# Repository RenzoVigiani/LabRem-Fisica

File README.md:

# Laboratorios de Física básica
En este readme se detallan las partes mas importantes del proyecto de remotización del laboratorio de física básica, haciendo énfacis en el hardware.

## Protocolo para los laboratorios de "Física básica"
Para poder establecer una comunicación entre al api web, generada por el equipo de software del proyecto, y los dispositivos en el laboratorio establecemos un protocolo en común. 

El procedimiento de comunicación es el siguiente. Cada vez que se quiere modificar algun dato en el laboratorio. El Servidor debe enviar un:
```Ruby 
POST /HTTP/1.1 + <JSON a enviar>
```
#### Json a enviar (ejemplo)
```Ruby  
{ "Estado": [0,true,false],"Analogico": [1,125,542,2]}
```
Y para obtener avances de los datos o reporte de los datos debe enviar un:
```Ruby 
GET /HTTP/1.1
```
De esta forma el Arduino responde ante una petición.

#### Json a recibir (ejemplo)

```Ruby  
{ "Estado": [0,true,false],"Analogico": [1,125,542,2], "Error": "Mensaje de error"}
```

## Sintaxis

**Estado:** Es un array conformado por 3 elementos en el siguiente orden: [Laboratorio, SubLab, Inicio del experimento]

|Laboratorio  | Sub Laboratorio  | Inicio del experimento | Laboratorio Seleccionado | Estado del experimento|
|-|-----|-----|-----------------|--------|
|3|true |true |Lente Convergente|Inicia  |
|3|true |false|Lente Convergente|Finaliza|
|3|false|true |Lente Divergente |Inicia  |
|3|false|false|Lente Divergente |Finaliza|

**Elementos por Laboratorio**

***Convergente***

- Analogico: [Tipo_Diafragma,Distancia_FL,Distancia_LP]
    
    Distancia_FL: Corresponde a la distancia entre Foco y Lente.
    
    Distancia_LP: Corresponde a la distancia entre Lente y Pantalla.

- Tipo_Diafragma = Indica el tipo de diafragma
  - 0 : Sin diafragma
  - 1 : Central
  - 2 : Periferico
  - 3 : Filtro Rojo

***Divergente***

```Ruby 
Analogico:[Tipo_Diafragma, Distancia_FL1, Distancia_L2P, Distancia_L1L2]
```
- Distancia_FL1: Corresponde a la distancia entre Foco y Lente Divergente.
- Distancia_L2P: Corresponde a la distancia entre Lente convergente y Pantalla.
- Distancia_L1L2: Corresponde a la distancia entre Lente divergente y convergente.

## Valores permitidos

Los valores permitidos en las distancias son:

| Distancia          |Valor mín|Valor máx| Unidad |
| ------------------ |---------|---------|--------|
|FL: Foco Lente      |   120   |   970   |  [mm]  |
|LP: Lente Pantalla  |    70   |   970   |  [mm]  |
|FL1: Foco Lente1    |    50   |   920   |  [mm]  |
|L1L2: Lente1 Lente2 |    70   |   900   |  [mm]  |
|L2P: Lente2 Pantalla|    70   |   970   |  [mm]  |

Se puede observar en la imagen las distancias especificadas. Se consideran margenes entre los soportes por seguridad.

**Error:** Es una variable numerica que representa un mensaje de error. 

| Tipo de error                     |  Valor  |
|-----------------------------------|---------|
| Sin errores                       |    0    |
| Error de distancia                |    1    |
| Error de tipo de diafragma        |    2    |
| Error de laboratorio incorrecto   |    3    |

## Diagramas
Para poder conectar la api web con los actuadores utilizamos un Arduino Mega 2560 y una placa creada por el equipo de hardware. 

Esta placa incorpora todos los drivers e indicadores necesarios para el funcionamiento del laboratorio.

**Arduino Mega 2560: PinOut**

||**ESQUEMÁTICO**||
|-|-|-|
||||

||**PCB**||
|-|-|-|
||||
||||
||||
||||
||||

**Diagrama general**

**Diagrama Vista superior**

**Diagrama Vista frontal**

**Datasheets Actuadores**
- [Recopilación de Datasheets](https://renzovigiani.notion.site/adea4f735c994faaa2f919a7e5105e9d?v=83070c8c05d34c02905fc370e37b802a)
- [Servo Motor MG966R](https://github.com/RenzoVigiani/LabRem-Fisica/blob/main/datasheets/MG996R-Datasheet.pdf)
- [Motor Paso a paso](https://github.com/RenzoVigiani/LabRem-Fisica/blob/main/datasheets/MG996R-Datasheet.pdf)
- [Lampara Led](http://wayjun.com/Datasheet/Led/3W%20High%20Power%20LED.pdf)

**Soportes 3D**

 A continuación se pueden ver los elementos diseñados por el equipo de hardware y luego creados a partir de una impresora 3D. Esto permitió generar soportes y gabinetes de acuerdo a los requerimientos y logrando mayor flexibilidad.

Se pueden ver los soportes creados para el sistema de movimiento de todo el ensayo. Se muestran:
- 4 bases para las lentes y el movimiento sobre los rieles.
- 3 soportes para motores paso a paso.
- 1 gabinete para soporte de foco o fuente de luz.
- 1 soporte para la pantalla.

|            |   |
|-------------------------|---------|
|   |    |
| ||
|   |   |
|  |  |
|  |  |
|  |  |

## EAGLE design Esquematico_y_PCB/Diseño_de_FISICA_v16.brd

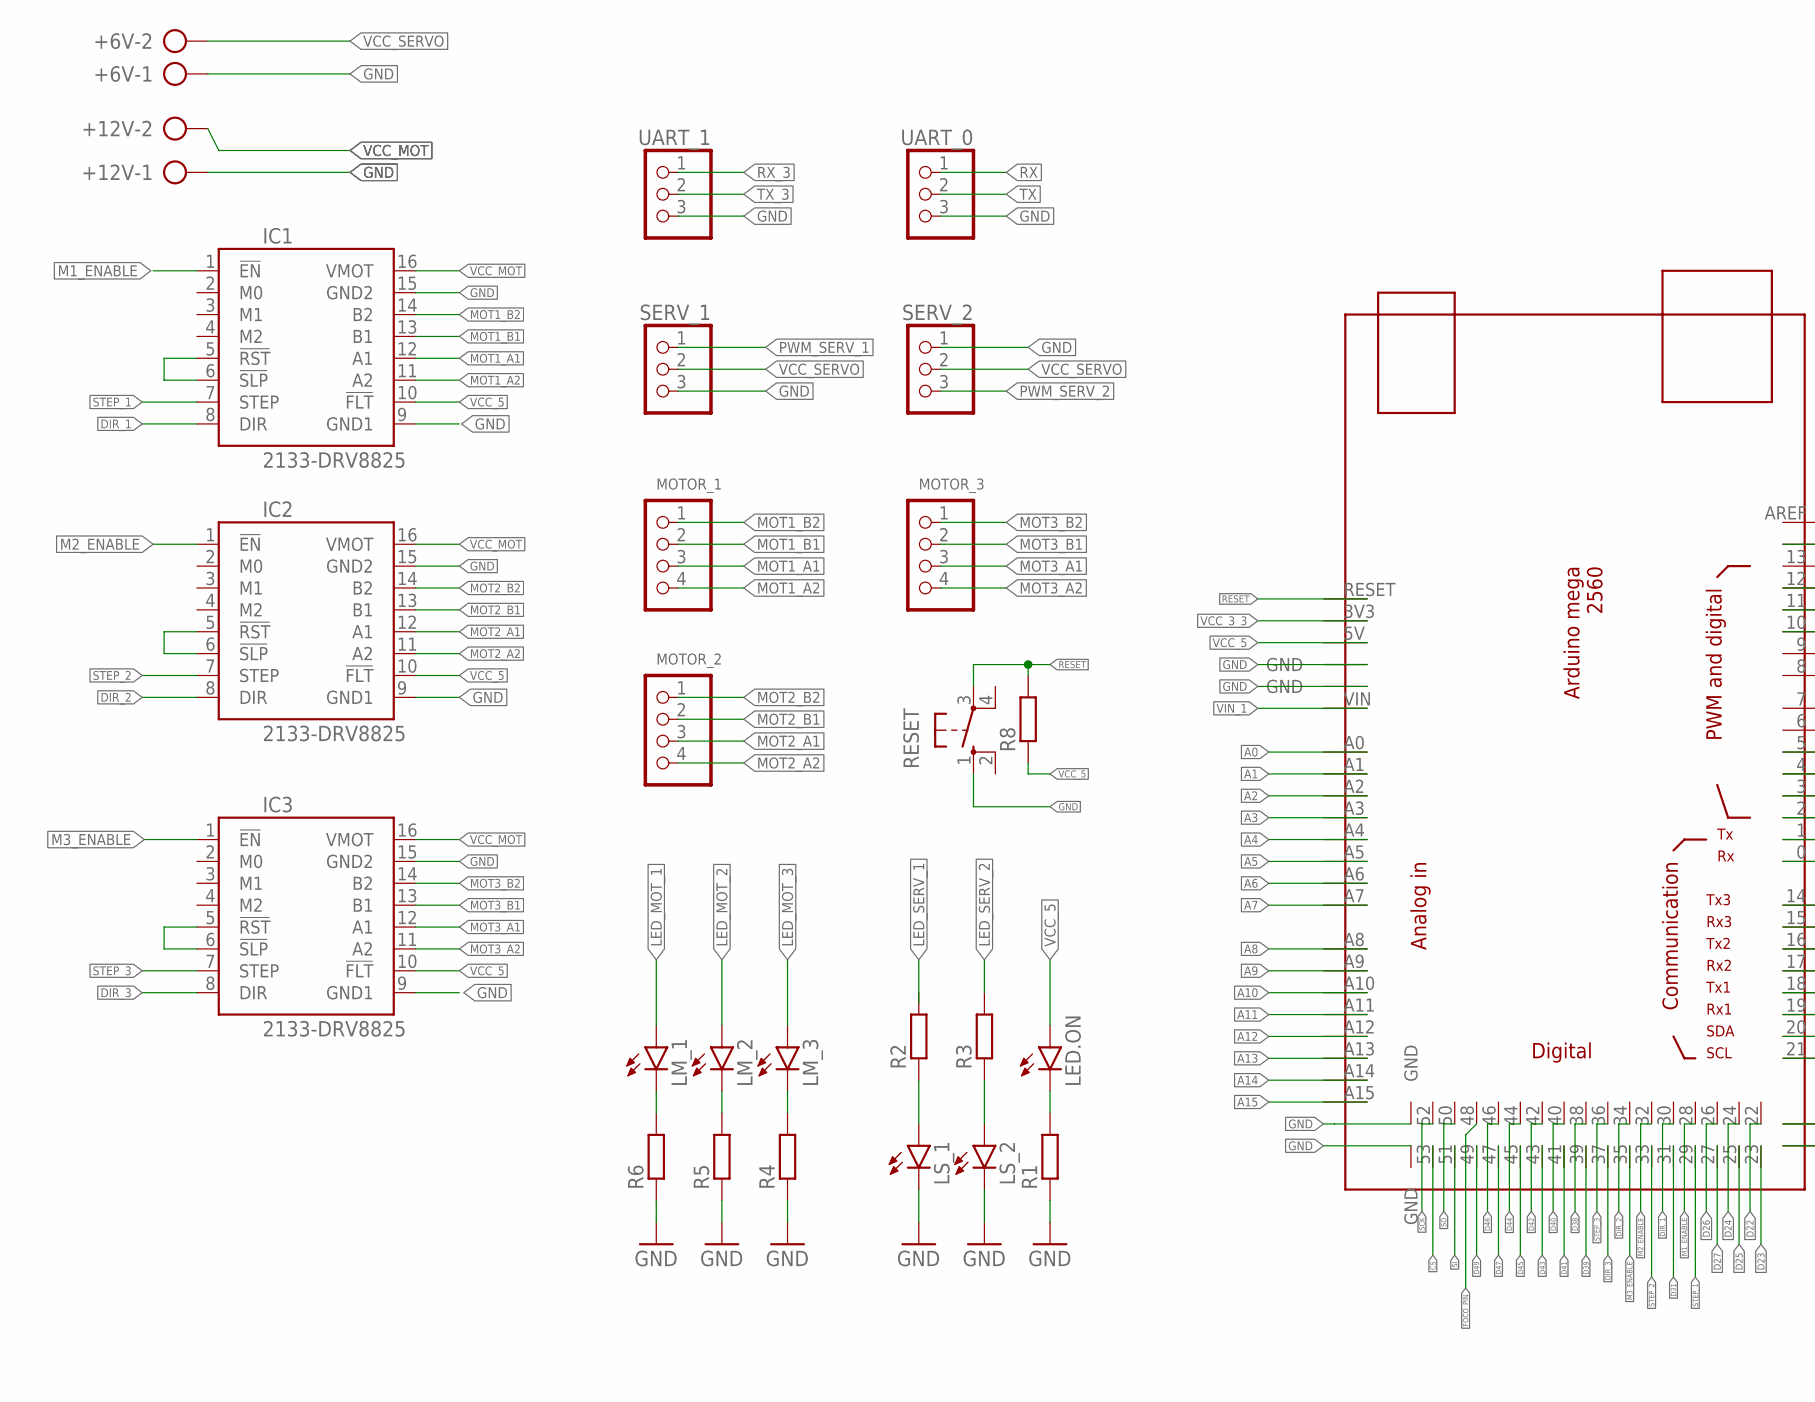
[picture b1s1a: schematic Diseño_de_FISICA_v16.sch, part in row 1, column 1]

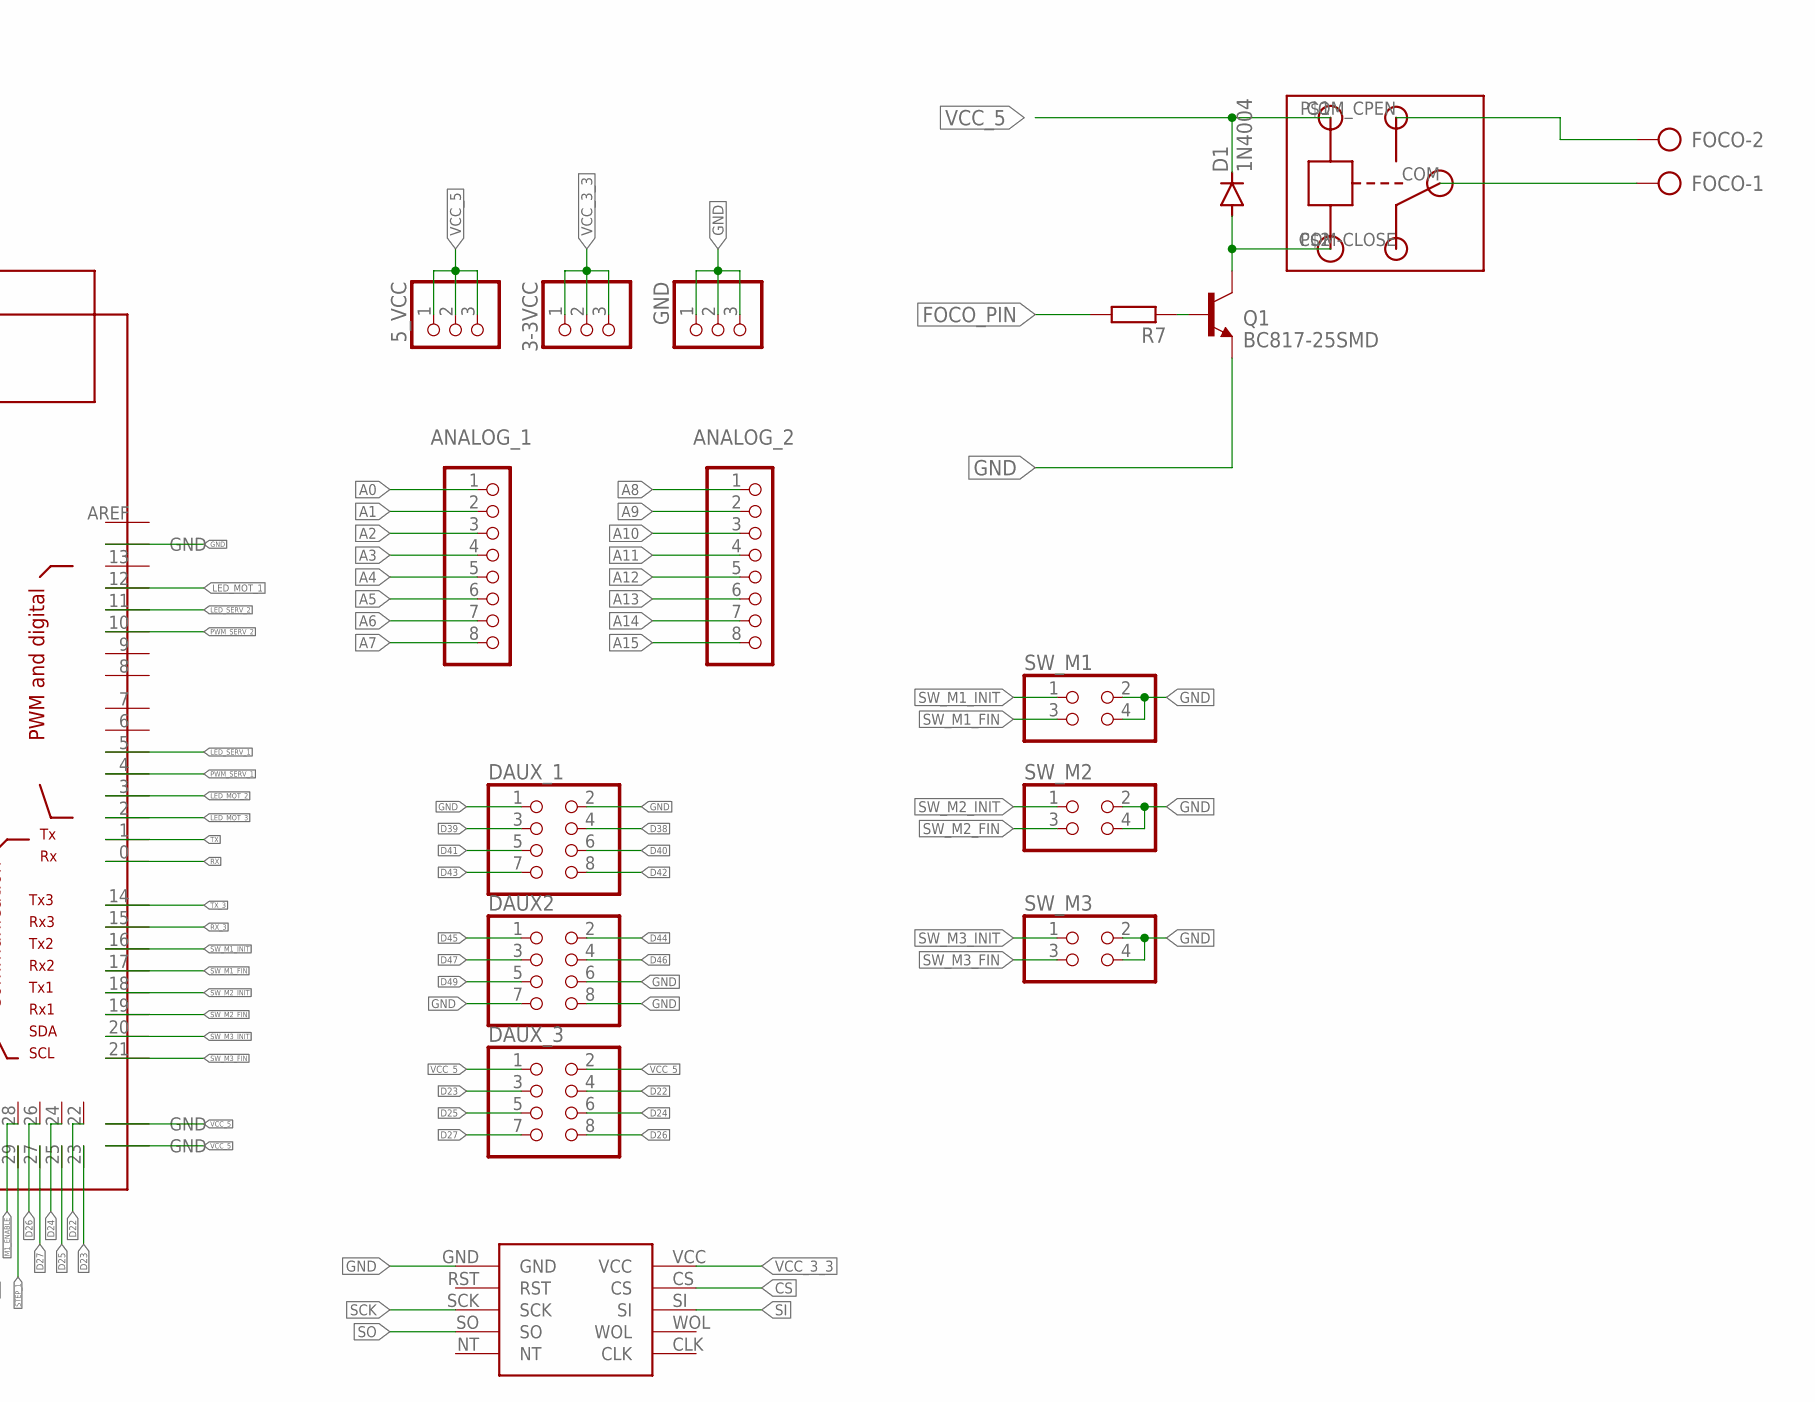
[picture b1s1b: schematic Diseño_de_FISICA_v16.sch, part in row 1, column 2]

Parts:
3-3VCC, 5_VCC: PINHD-1X3; 1X03
+6V, +12V: AK300/2
ANALOG_1, ANALOG_2: PINHD-1X8; 1X08
ARDUINOMEGA2560: MEGA_DEVICE; MEGAOUTLINE
D1: 1N4004; DO41-10
DAUX2: PINHD-2X4; 2X04
DAUX_1, DAUX_3: PINHD-2X4; 2X04
FOCO: AK300/2
GND: PINHD-1X3; 1X03
IC1, IC2, IC3: 2133-DRV8825; DRV8825
LED.ON: LED3MM
LM_1, LM_2, LM_3: LED3MM
LS_1, LS_2: LED3MM
MODULO_ETHERNET: ENC28J60
MOTOR_1, MOTOR_2, MOTOR_3: PINHD-1X4; 1X04
Q1: BC817-25SMD; SOT23-BEC
R1, R2, R3, R4, R5, R6, R7, R8: R_CHIP-0805(2012-METRIC); RESC2012X65
RESET: 10-XX; B3F-10XX
SERV_1, SERV_2: PINHD-1X3; 1X03
SW_M1, SW_M2, SW_M3: PINHD-2X2; 2X02
U$1: RELAY
UART_0, UART_1: PINHD-1X3; 1X03

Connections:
A0: ANALOG_1.1, ARDUINOMEGA2560.A0
A1: ANALOG_1.2, ARDUINOMEGA2560.A1
A2: ANALOG_1.3, ARDUINOMEGA2560.A2
A3: ANALOG_1.4, ARDUINOMEGA2560.A3
A4: ANALOG_1.5, ARDUINOMEGA2560.A4
A5: ANALOG_1.6, ARDUINOMEGA2560.A5
A6: ANALOG_1.7, ARDUINOMEGA2560.A6
A7: ANALOG_1.8, ARDUINOMEGA2560.A7
A8: ANALOG_2.1, ARDUINOMEGA2560.A8
A9: ANALOG_2.2, ARDUINOMEGA2560.A9
A10: ANALOG_2.3, ARDUINOMEGA2560.A10
A11: ANALOG_2.4, ARDUINOMEGA2560.A11
A12: ANALOG_2.5, ARDUINOMEGA2560.A12
A13: ANALOG_2.6, ARDUINOMEGA2560.A13
A14: ANALOG_2.7, ARDUINOMEGA2560.A14
A15: ANALOG_2.8, ARDUINOMEGA2560.A15
CS: ARDUINOMEGA2560.53, MODULO_ETHERNET.CS
D22: ARDUINOMEGA2560.22, DAUX_3.4
D23: ARDUINOMEGA2560.23, DAUX_3.3
D24: ARDUINOMEGA2560.24, DAUX_3.6
D25: ARDUINOMEGA2560.25, DAUX_3.5
D26: ARDUINOMEGA2560.26, DAUX_3.8
D27: ARDUINOMEGA2560.27, DAUX_3.7
D31: ARDUINOMEGA2560.31
D38: ARDUINOMEGA2560.38, DAUX_1.4
D39: ARDUINOMEGA2560.39, DAUX_1.3
D40: ARDUINOMEGA2560.40, DAUX_1.6
D41: ARDUINOMEGA2560.41, DAUX_1.5
D42: ARDUINOMEGA2560.42, DAUX_1.8
D43: ARDUINOMEGA2560.43, DAUX_1.7
D44: ARDUINOMEGA2560.44, DAUX2.2
D45: ARDUINOMEGA2560.45, DAUX2.1
D46: ARDUINOMEGA2560.46, DAUX2.4
D47: ARDUINOMEGA2560.47, DAUX2.3
D49: ARDUINOMEGA2560.49, DAUX2.5
DIR_1: ARDUINOMEGA2560.30, IC1.8 (DIR)
DIR_2: ARDUINOMEGA2560.34, IC2.8 (DIR)
DIR_3: ARDUINOMEGA2560.37, IC3.8 (DIR)
FOCO_PIN: ARDUINOMEGA2560.48, R7.2
GND: +6V.1, +12V.1, ARDUINOMEGA2560.GND@1 (GND), ARDUINOMEGA2560.GND@2 (GND), ARDUINOMEGA2560.GND@3 (GND), ARDUINOMEGA2560.GND@6 (GND), ARDUINOMEGA2560.GND@7 (GND), DAUX2.6, DAUX2.7, DAUX2.8, DAUX_1.1, DAUX_1.2, GND.1, GND.2, GND.3, IC1.9 (GND1), IC1.15 (GND2), IC2.9 (GND1), IC2.15 (GND2), IC3.9 (GND1), IC3.15 (GND2), LS_1.K (C), LS_2.K (C), MODULO_ETHERNET.GND, Q1.E, R1.1, R4.1, R5.1, R6.1, RESET.1 (S), SERV_1.3, SERV_2.1, SW_M1.2, SW_M1.4, SW_M2.2, SW_M2.4, SW_M3.2, SW_M3.4, UART_0.3, UART_1.3
LED_MOT_1: ARDUINOMEGA2560.12, LM_1.A
LED_MOT_2: ARDUINOMEGA2560.3, LM_2.A
LED_MOT_3: ARDUINOMEGA2560.2, LM_3.A
LED_SERV_1: ARDUINOMEGA2560.5, R2.2
LED_SERV_2: ARDUINOMEGA2560.11, R3.2
M1_ENABLE: ARDUINOMEGA2560.28, IC1.1 (!EN)
M2_ENABLE: ARDUINOMEGA2560.32, IC2.1 (!EN)
M3_ENABLE: ARDUINOMEGA2560.35, IC3.1 (!EN)
MOT1_A1: IC1.12 (A1), MOTOR_1.3
MOT1_A2: IC1.11 (A2), MOTOR_1.4
MOT1_B1: IC1.13 (B1), MOTOR_1.2
MOT1_B2: IC1.14 (B2), MOTOR_1.1
MOT2_A1: IC2.12 (A1), MOTOR_2.3
MOT2_A2: IC2.11 (A2), MOTOR_2.4
MOT2_B1: IC2.13 (B1), MOTOR_2.2
MOT2_B2: IC2.14 (B2), MOTOR_2.1
MOT3_A1: IC3.12 (A1), MOTOR_3.3
MOT3_A2: IC3.11 (A2), MOTOR_3.4
MOT3_B1: IC3.13 (B1), MOTOR_3.2
MOT3_B2: IC3.14 (B2), MOTOR_3.1
unnamed: FOCO.2, U$1.COM_CPEN (COM-OPEN)
unnamed: D1.A, Q1.C, U$1.P$2 (GND)
unnamed: FOCO.1, U$1.COM
unnamed: Q1.B, R7.1
unnamed: LS_1.A, R2.1
unnamed: LS_2.A, R3.1
unnamed: IC2.5 (!RST), IC2.6 (!SLP)
unnamed: IC1.5 (!RST), IC1.6 (!SLP)
unnamed: IC3.5 (!RST), IC3.6 (!SLP)
unnamed: LED.ON.K (C), R1.2
unnamed: LM_3.K (C), R4.2
unnamed: LM_2.K (C), R5.2
unnamed: LM_1.K (C), R6.2
PWM_SERV_1: ARDUINOMEGA2560.4, SERV_1.1
PWM_SERV_2: ARDUINOMEGA2560.10, SERV_2.3
RESET: ARDUINOMEGA2560.RESET, R8.2, RESET.3
RX: ARDUINOMEGA2560.0, UART_0.1
RX_3: ARDUINOMEGA2560.15, UART_1.1
SCK: ARDUINOMEGA2560.52, MODULO_ETHERNET.SCK
SI: ARDUINOMEGA2560.51, MODULO_ETHERNET.SI
SO: ARDUINOMEGA2560.50, MODULO_ETHERNET.SO
STEP_1: ARDUINOMEGA2560.29, IC1.7 (STEP)
STEP_2: ARDUINOMEGA2560.33, IC2.7 (STEP)
STEP_3: ARDUINOMEGA2560.36, IC3.7 (STEP)
SW_M1_FIN: ARDUINOMEGA2560.17, SW_M1.3
SW_M1_INIT: ARDUINOMEGA2560.16, SW_M1.1
SW_M2_FIN: ARDUINOMEGA2560.19, SW_M2.3
SW_M2_INIT: ARDUINOMEGA2560.18, SW_M2.1
SW_M3_FIN: ARDUINOMEGA2560.21, SW_M3.3
SW_M3_INIT: ARDUINOMEGA2560.20, SW_M3.1
TX: ARDUINOMEGA2560.1, UART_0.2
TX_3: ARDUINOMEGA2560.14, UART_1.2
VCC_3_3: 3-3VCC.1, 3-3VCC.2, 3-3VCC.3, ARDUINOMEGA2560.3V3, MODULO_ETHERNET.VCC
VCC_5: 5_VCC.1, 5_VCC.2, 5_VCC.3, ARDUINOMEGA2560.5V, ARDUINOMEGA2560.GND@4 (GND), ARDUINOMEGA2560.GND@5 (GND), D1.C, DAUX_3.1, DAUX_3.2, IC1.10 (!FLT), IC2.10 (!FLT), IC3.10 (!FLT), LED.ON.A, R8.1, U$1.P$1 (IN)
VCC_MOT: +12V.2, IC1.16 (VMOT), IC2.16 (VMOT), IC3.16 (VMOT)
VCC_SERVO: +6V.2, SERV_1.2, SERV_2.2
VIN_1: ARDUINOMEGA2560.VIN

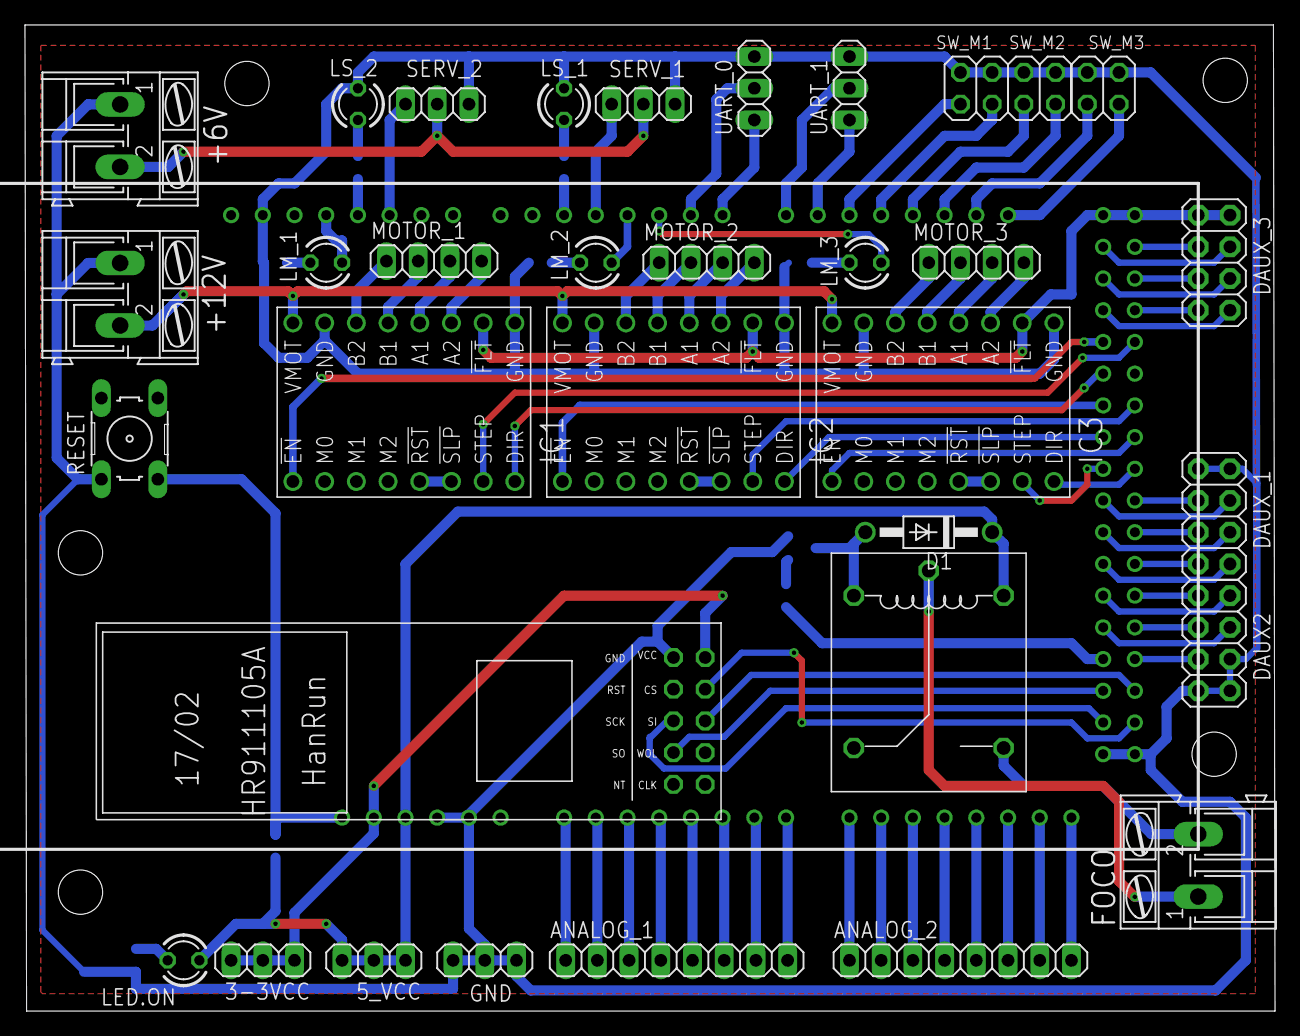
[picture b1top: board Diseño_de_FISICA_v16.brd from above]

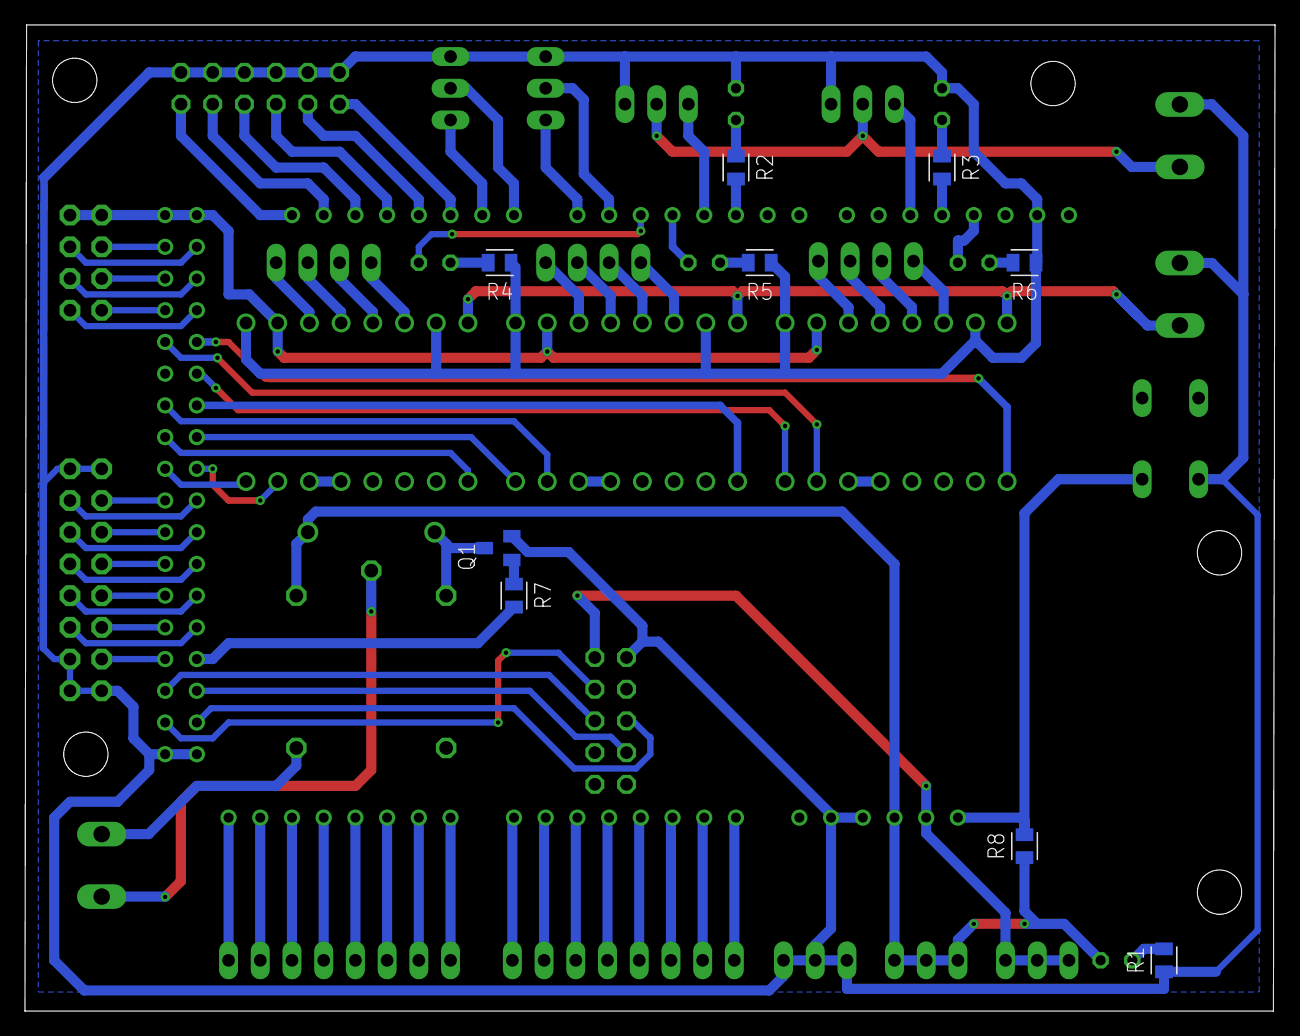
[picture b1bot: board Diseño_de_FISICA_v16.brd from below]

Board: 2 copper layers, 100.1 x 79.0 mm, 44 parts (9 on the bottom side), 95 nets.

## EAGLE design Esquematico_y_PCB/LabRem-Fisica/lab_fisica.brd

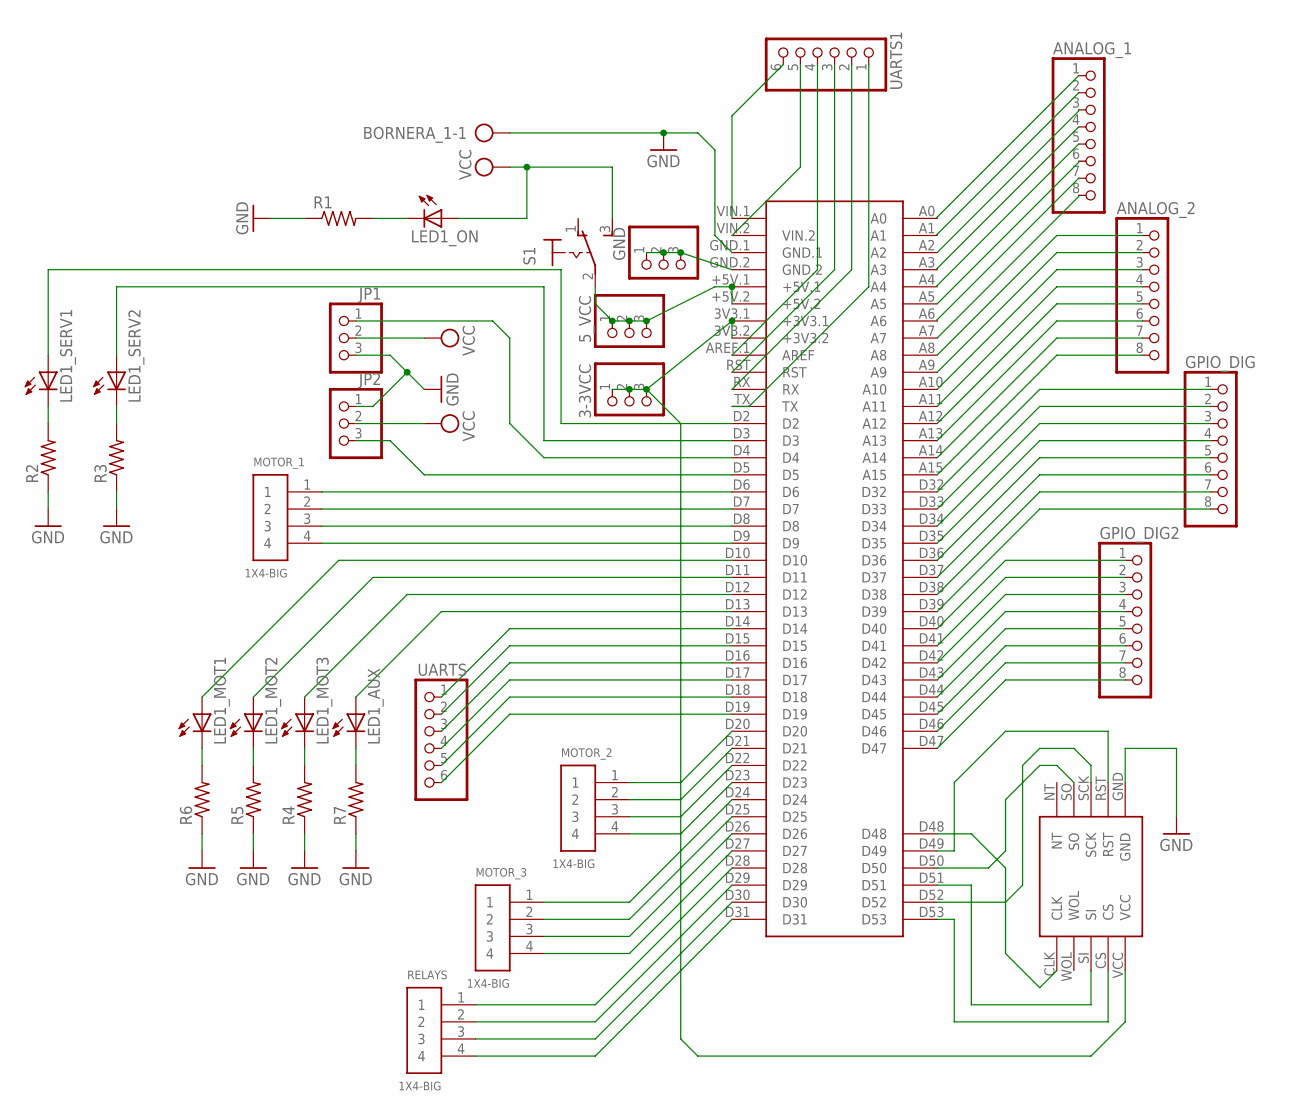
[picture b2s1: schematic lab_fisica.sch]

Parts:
3-3VCC, 5_VCC: PINHD-1X3; 1X03
ANALOG_1, ANALOG_2: PINHD-1X8BIG; 1X08-BIG
BORNERA_1: AK300/2
GND: PINHD-1X3; 1X03
GPIO_DIG, GPIO_DIG2: PINHD-1X8BIG; 1X08-BIG
JP1, JP2: PINHD-1X3; 1X03
LED1_AUX, LED1_MOT1, LED1_MOT2, LED1_MOT3, LED1_ON, LED1_SERV1, LED1_SERV2: LED5MM
MODULO_ETHERNET: ENC28J60
MOTOR_1, MOTOR_2, MOTOR_3: 1X4-BIG; 1X04-BIG
R1, R2, R3, R4, R5, R6, R7: R-US_R0805; R0805
RELAYS: 1X4-BIG; 1X04-BIG
S1: 320-916
U$1: MEGA2560_MIKRO
UARTS, UARTS1: PINHD-1X6B; 1X06-BIG

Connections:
GND: BORNERA_1.1, JP1.3, JP2.1, MODULO_ETHERNET.GND, R1.1, R2.1, R3.1, R4.1, R5.1, R6.1, R7.1, U$1.GND.1
unnamed: MODULO_ETHERNET.SO, U$1.D50
unnamed: MODULO_ETHERNET.SI, U$1.D51
unnamed: MODULO_ETHERNET.CS, U$1.D53
unnamed: MODULO_ETHERNET.SCK, U$1.D52
unnamed: GND.1, GND.2, GND.3, U$1.GND.2
unnamed: JP2.3, U$1.D5
unnamed: JP1.1, U$1.D4
unnamed: MOTOR_1.1, U$1.D6
unnamed: MOTOR_1.2, U$1.D7
unnamed: MOTOR_1.3, U$1.D8
unnamed: MOTOR_1.4, U$1.D9
unnamed: MOTOR_2.4, U$1.D23
unnamed: MOTOR_2.3, U$1.D22
unnamed: MOTOR_2.2, U$1.D21
unnamed: MOTOR_2.1, U$1.D20
unnamed: MOTOR_3.1, U$1.D24
unnamed: MOTOR_3.2, U$1.D25
unnamed: MOTOR_3.3, U$1.D26
unnamed: MOTOR_3.4, U$1.D27
unnamed: LED1_ON.K (C), R1.2
unnamed: LED1_SERV1.K (C), R2.2
unnamed: LED1_SERV2.K (C), R3.2
unnamed: LED1_MOT3.K (C), R4.2
unnamed: LED1_MOT2.K (C), R5.2
unnamed: LED1_MOT1.K (C), R6.2
unnamed: U$1.D19, UARTS.6
unnamed: U$1.D18, UARTS.5
unnamed: U$1.D17, UARTS.4
unnamed: LED1_SERV2.A, U$1.D3
unnamed: LED1_SERV1.A, U$1.D2
unnamed: U$1.D16, UARTS.3
unnamed: U$1.D15, UARTS.2
unnamed: U$1.D14, UARTS.1
unnamed: LED1_AUX.A, U$1.D13
unnamed: LED1_MOT3.A, U$1.D12
unnamed: LED1_MOT2.A, U$1.D11
unnamed: LED1_AUX.K (C), R7.2
unnamed: LED1_MOT1.A, U$1.D10
unnamed: RELAYS.1, U$1.D28
unnamed: RELAYS.2, U$1.D29
unnamed: RELAYS.3, U$1.D30
unnamed: RELAYS.4, U$1.D31
unnamed: 5_VCC.1, 5_VCC.2, 5_VCC.3, S1.2, U$1.+5V.1, U$1.+5V.2
unnamed: 3-3VCC.1, 3-3VCC.2, 3-3VCC.3, MODULO_ETHERNET.VCC, U$1.3V3.1 (+3V3.1), U$1.3V3.2 (+3V3.2)
unnamed: U$1.TX, UARTS1.1
unnamed: U$1.RX, UARTS1.2
unnamed: U$1.RST, UARTS1.3
unnamed: U$1.AREF.1 (AREF), UARTS1.4
unnamed: U$1.VIN.2, UARTS1.5
unnamed: U$1.VIN.1, UARTS1.6
unnamed: MODULO_ETHERNET.RST, U$1.D49
unnamed: MODULO_ETHERNET.CLK, U$1.D48
unnamed: ANALOG_1.1, U$1.A0
unnamed: ANALOG_1.2, U$1.A1
unnamed: ANALOG_1.3, U$1.A2
unnamed: ANALOG_1.4, U$1.A3
unnamed: ANALOG_1.5, U$1.A4
unnamed: ANALOG_1.6, U$1.A5
unnamed: ANALOG_1.7, U$1.A6
unnamed: ANALOG_1.8, U$1.A7
unnamed: ANALOG_2.1, U$1.A8
unnamed: ANALOG_2.2, U$1.A9
unnamed: ANALOG_2.3, U$1.A10
unnamed: ANALOG_2.4, U$1.A11
unnamed: ANALOG_2.5, U$1.A12
unnamed: ANALOG_2.6, U$1.A13
unnamed: ANALOG_2.7, U$1.A14
unnamed: ANALOG_2.8, U$1.A15
unnamed: GPIO_DIG.1, U$1.D32
unnamed: GPIO_DIG.2, U$1.D33
unnamed: GPIO_DIG.3, U$1.D34
unnamed: GPIO_DIG.4, U$1.D35
unnamed: GPIO_DIG.5, U$1.D36
unnamed: GPIO_DIG.6, U$1.D37
unnamed: GPIO_DIG.7, U$1.D38
unnamed: GPIO_DIG.8, U$1.D39
unnamed: GPIO_DIG2.1, U$1.D40
unnamed: GPIO_DIG2.2, U$1.D41
unnamed: GPIO_DIG2.3, U$1.D42
unnamed: GPIO_DIG2.4, U$1.D43
unnamed: GPIO_DIG2.5, U$1.D44
unnamed: GPIO_DIG2.6, U$1.D45
unnamed: GPIO_DIG2.7, U$1.D46
unnamed: GPIO_DIG2.8, U$1.D47
VCC: JP1.2, JP2.2, LED1_ON.A, S1.3 (S)

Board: 2 copper layers, 33 parts (0 on the bottom side), 86 nets, no tracks yet.
